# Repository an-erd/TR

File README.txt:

PURPOSE
=======
The function of TR is to have a tiny gym timer, which can give you intervals for active and rest
phases during gym or any other sport. Is has 4 buttons (1 reset button, and three functional
buttons T1..3 ), 9 leds (5 red as a progress bar, 3 orange for current phase active or rest, 
resp. (or during config), and a green heartbeat led.)
It is build on an ATMEL ATMEGA328P, but should work on any other similar MCU, too.
The power is assumed to be 3V. The code is optimized for power saving, but since the leds draw a
pretty high load, it is - by system - still consuming around 10 mA on average during training.

The program flow exist of the following steps:
- initialization (I/O pins, timer, ...)
- configuration routine
- training routine

During the phases, to control is done with the buttons, and the leds change the mode accordingly.
The specific status and control is shown in the list below.

The program itself makes heavy use of two timer, and pin change interrupts. The logic itself, in 
particular waiting for a counter to run down and to give effects and progress with the leds is
more or less completly delivered by the relevant interrupts. 

During WAITING MODE
====================
	LED PB1/green		-> slow flashing means "waiting for command"
	T1					-> choose subprog (timer, metronome, light effects)
	T2					-> go into config mode
	T3					-> GO! (fire chosen subprog)

	LED PD0..7/red/ora	-> off
	LED PB1/green		-> short heartbeat

During CHOOSE_SUBPROG
=====================
	T1					-> increase subprog counter w/wrap-around
	T2					-> n/a
	T3					-> exit choose subprog function

	LED PD0..4/red		-> show configurated value
	LED PD5..7/orange	-> n/a = OFF
	LED PB1/green		-> fast flashing

During CONFIG
=============
	T1					-> increase config parameter value, wrap-arolund 5 -> 1 or 0 resp.
	T2					-> switch to next config parameter, wrap-around is done
	T3					-> GO! fire chosen subprog)

	LED PD0..4/red		-> show configurated value
	LED PD5..7/orange	-> show configuration step (000/INT, 100/ACT, 110/REST, 111/cycles)
	LED PB1/green		-> fast flashing

During TRAINING
===============
	T1					-> (nothing yet)
	T2					-> Stop training and go in "waiting mode", see main loop
	T3					-> Pause training

	LED PD0..4/red		-> show progress in current phase, current step flashes, 1-5 leds
	LED PD5..7/orange	-> show LR or RL cascade to show phase ACTIVE or REST, resp.
	LED PB1/green		-> heartbeat

During PAUSE
============
	LED PD0..4/red		-> freeze current status 
	LED PD5..7/orange	-> freeze current status
	LED PB1/green		-> slow flashing

	T2					-> Stop training/pause and go in "waiting mode", see main loop
	T3					-> end pause, 

TODO and optimization
=====================
- none yet

EEPROM usage for permanently store configuration parameter
==========================================================
uint8_t	EEMEM subprog_param_ee: goes to program_status.subprog_param
set to 
    SUBPROG_TIMER
    SUBPROG_METRONOME
    SUBPROG_LIGHT_EFFECT

uint8_t	EEMEM config_params_ee[NUM_SUBPROGS][NUM_CONFIG_PARAMS] to store values in(maybe a little waste of space)

Timer calculation/values
========================
- 8 MHz quartz, fuse CKDIV8 disabled, F_CPU=8000000UL
- timer0: 8 MHz,  8bit, 1/64  prescale -> 1 KHz (OCR0A   125 ticks / .001s=1ms)
- timer1: 8 MHz, 16bit, 1/256 prescale -> 1 Hz  (OCR1A 31250 Ticks / 1s, OCR1B 3125 Ticks / .1s)

- 8 MHz quartz, fuse CKDIV8 set, F_CPU=1000000UL
- timer0: @F_CPU/8, tick values stay unchanged
- timer1: @F_CPU/64, 1 Hz: OCR1A = 15625, 10 Hz: OCR1B =  1562

FUSE Settings are:
==================
BODLEVEL = 1V8
RSTDISBL = [ ]
DWEN = [ ]
SPIEN = [X]
WDTON = [ ]
EESAVE = [X]
BOOTSZ = 2048W_3800
BOOTRST = [ ]
CKDIV8 = [X]
CKOUT = [ ]
SUT_CKSEL = EXTXOSC_8MHZ_XX_16KCK_14CK_65MS

EXTENDED = 0xFE (valid)
HIGH = 0xD1 (valid)
LOW = 0x7F (valid)

Compiler symbols defined
========================
F_CPU=1000000UL
_PRODUCTION_TEST_ROUTINE_
_ALL_LED_ON_FOR_5_SEC_
_INCREASE_NUM_LED_ON_

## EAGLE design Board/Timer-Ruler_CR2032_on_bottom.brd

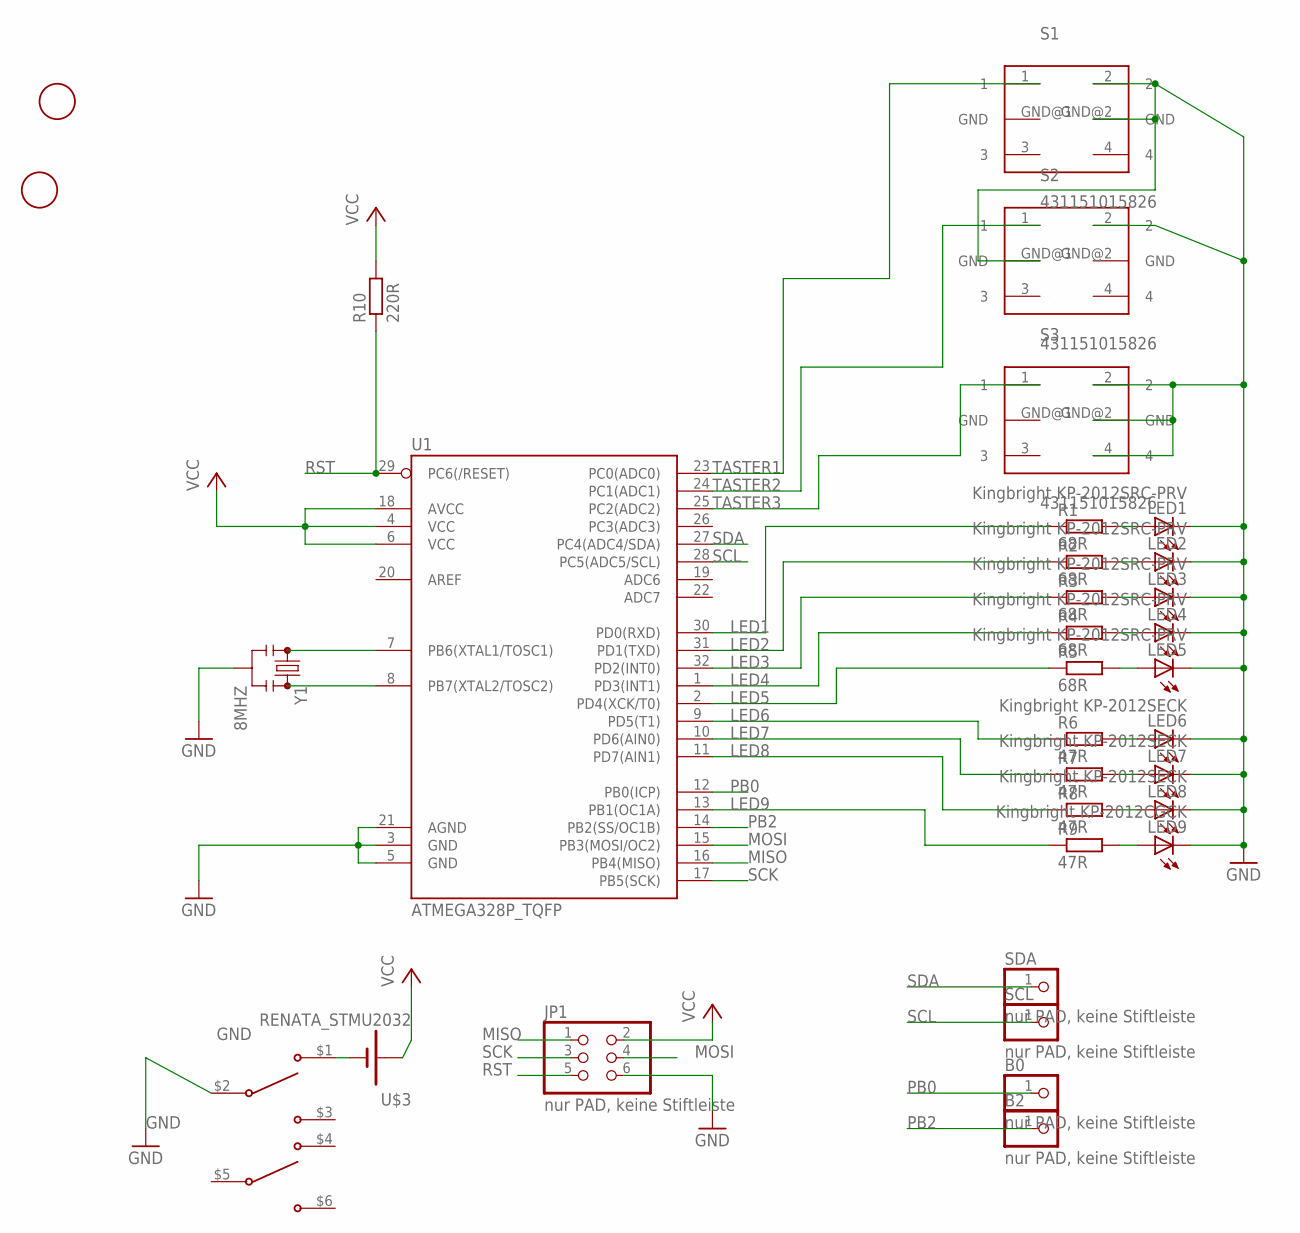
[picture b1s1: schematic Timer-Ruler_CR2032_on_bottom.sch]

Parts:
B0, B2: nur PAD, keine Stiftleiste; 1X01
JP1: nur PAD, keine Stiftleiste; 2X03
LED1, LED2, LED3, LED4, LED5: Kingbright KP-2012SRC-PRV; CHIP-LED0805
LED6, LED7, LED8: Kingbright KP-2012SECK; CHIP-LED0805
LED9: Kingbright KP-2012CGCK; CHIP-LED0805
R1, R2, R3, R4, R5: 68R; R0402
R6, R7, R8, R9: 47R; R0402
R10: 220R; R0402
S1, S2, S3: 431151015826; 431181015816
SCL: nur PAD, keine Stiftleiste; 1X01
SDA: nur PAD, keine Stiftleiste; 1X01
U1: ATMEGA328P_TQFP; TQFP32-08
U$1, U$2: FIDUCIAL; FIDUCIAL_1MM
U$3: RENATA_STMU2032; SMTU2032
U$4: C+K_AYZ0202AGRLC
Y1: 8MHZ; RESONATOR-SMD

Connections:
GND: JP1.6, LED1.C, LED2.C, LED3.C, LED4.C, LED5.C, LED6.C, LED7.C, LED8.C, LED9.C, S1.2, S1.GND@2 (GND), S2.2, S2.GND@1 (GND), S3.2, S3.4, S3.GND@2 (GND), U1.3 (GND), U1.5 (GND), U1.21 (AGND), U$4.$2 (2), Y1.2
LED1: R1.1, U1.30 (PD0(RXD))
LED2: R2.1, U1.31 (PD1(TXD))
LED3: R3.1, U1.32 (PD2(INT0))
LED4: R4.1, U1.1 (PD3(INT1))
LED5: R5.1, U1.2 (PD4(XCK/T0))
LED6: R6.1, U1.9 (PD5(T1))
LED7: R7.1, U1.10 (PD6(AIN0))
LED8: R8.1, U1.11 (PD7(AIN1))
LED9: R9.1, U1.13 (PB1(OC1A))
MISO: JP1.1, U1.16 (PB4(MISO))
MOSI: JP1.4, U1.15 (PB3(MOSI/OC2))
unnamed: LED1.A, R1.2
unnamed: LED2.A, R2.2
unnamed: LED3.A, R3.2
unnamed: LED4.A, R4.2
unnamed: LED5.A, R5.2
unnamed: LED6.A, R6.2
unnamed: LED7.A, R7.2
unnamed: LED8.A, R8.2
unnamed: LED9.A, R9.2
unnamed: U1.7 (PB6(XTAL1/TOSC1)), Y1.1
unnamed: U1.8 (PB7(XTAL2/TOSC2)), Y1.3
unnamed: U$3.-, U$4.$1 (1)
PB0: B0.1, U1.12 (PB0(ICP))
PB2: B2.1, U1.14 (PB2(SS/OC1B))
RST: JP1.5, R10.1, U1.29 (PC6(/RESET))
SCK: JP1.3, U1.17 (PB5(SCK))
SCL: SCL.1, U1.28 (PC5(ADC5/SCL))
SDA: SDA.1, U1.27 (PC4(ADC4/SDA))
TASTER1: S1.1, U1.23 (PC0(ADC0))
TASTER2: S2.1, U1.24 (PC1(ADC1))
TASTER3: S3.1, U1.25 (PC2(ADC2))
VCC: JP1.2, R10.2, U1.4 (VCC), U1.6 (VCC), U1.18 (AVCC), U$3.+

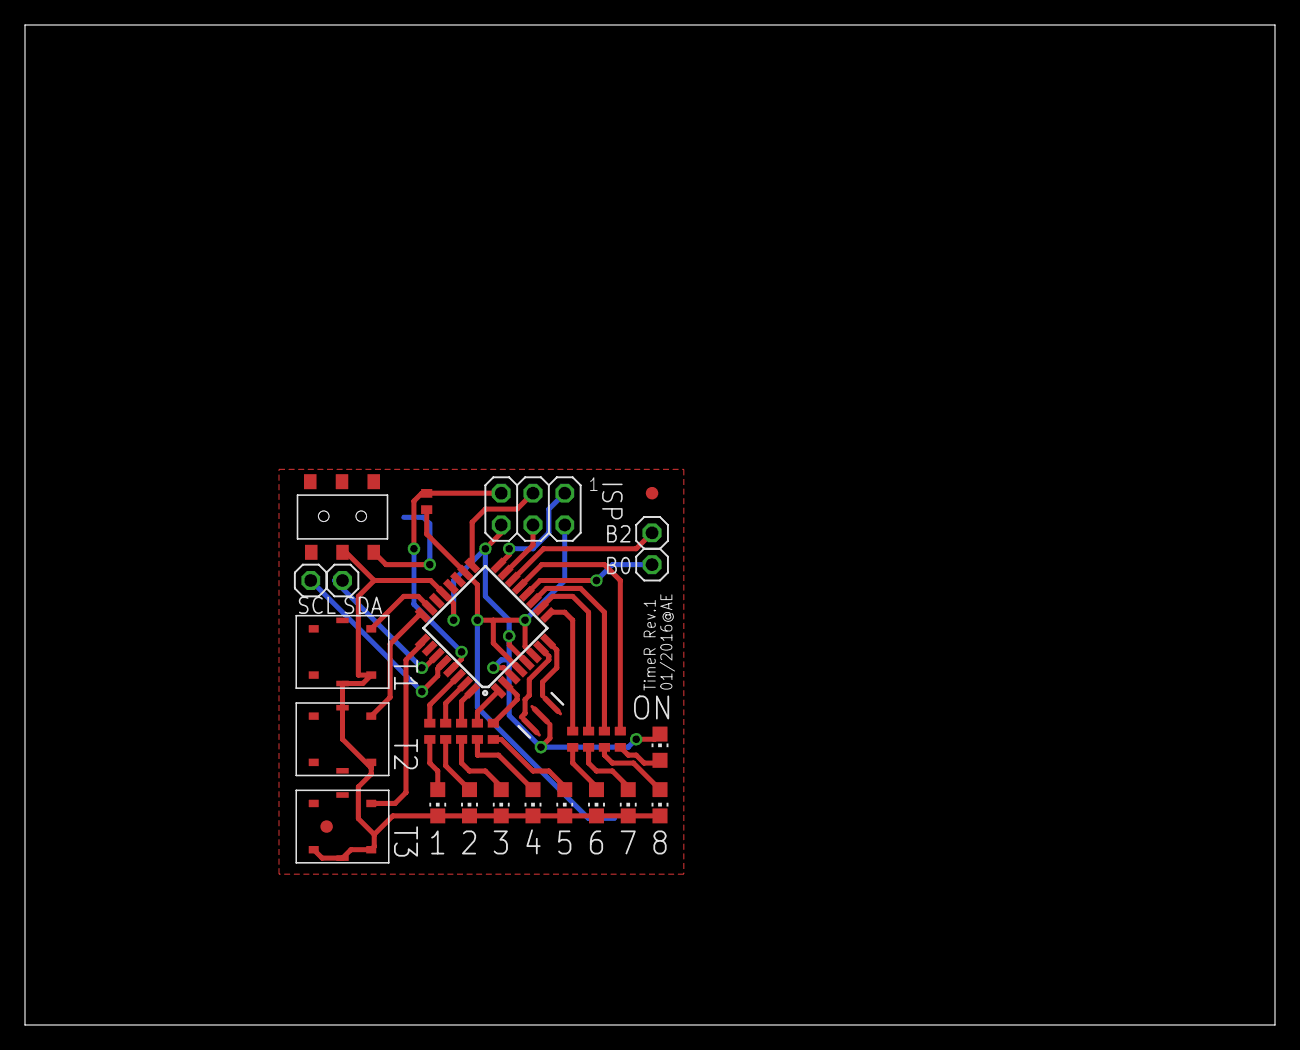
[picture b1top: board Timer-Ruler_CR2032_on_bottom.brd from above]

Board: 2 copper layers, 100.0 x 80.0 mm, 33 parts (1 on the bottom side), 34 nets.

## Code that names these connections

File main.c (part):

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 */ 

/* atmega328p ports used:
	 PC0	Switch T1	PCINT8		0
	 PC1	Switch T2	PCINT9		1
	 PC2	Switch T3	PCINT10		2
	(PC4	I2C SDA		unused)
	(PC5	I2C SCL		unused)
	 PD0	LED1 RED				0
	 PD1	LED2 RED				1
	 PD2	LED3 RED				2
	 PD3	LED4 RED				3
	 PD4	LED5 RED				4
	 PD5	LED6 ORANGE				5
	 PD6	LED7 ORANGE				6
	 PD7	LED8 ORANGE				7
	 PB1 	LED9 GREEN				8
*/

#include <avr/io.h>
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		
	// fired every 1ms gone

	// button debounce mechanism for T1..3 (PC0..2)
	// - the button is assumed to be stable if "pressed" status occurs 50x (=50ms) in a row
	// - temp_state_button_pressed is set in pin change interrupt routine (ISR (PCINT1_vect))
	//
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{
	volatile uint8_t changedbits;

	// Interrupt routine handles pin chance interrupts for PC0..2
	// if a button changes the state, .temp_state_button_pressed is updated
	// results are evaluated (in particular, debouncing) in ISR (TIMER0_COMPA_vect), 
	// and used throughout the program by program_status.Tx.button_pressed, which then need to be cleared again
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void init_io_pins(void)
{
	// power consumption 480 uA in IDLE mode -> 20.8 uA PWR_DOWN
	DDRB  = BIT(DDB1);				// PB1 as output, all other as input
	PORTB = 0xFD;					// all input w/pull-ups
	DDRC  = 0x00;					// all port C as input
	PORTC = 0x7F;					// PC0..2 used for switches, but set all w/pull-ups
	DDRD  = 0xFF;					// all port D as output (all PD0..7 used for LEDs)
	
	bit_set(PCICR,  BIT(PCIE1));							// pin change interrupt enable
	bit_set(PCMSK1, BIT(PCINT8)|BIT(PCINT9)|BIT(PCINT10) );	// Enable pin change detection
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	//		2 -> CONFIG_NR_INTERVAL_REST
	//		3 -> CONFIG_NR_CYCLES
	// do
	//		update orange leds PD5..7 with 0 to all three leds according to i
	//		press T1 X-times -> red leds PD0..4 show the count according to the click counter
	//		press T2 for next step in "for i" loop and wraparound 0->1->2->3->0
	//			or press T3 to leave configuration mode and GO!
	//	done
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	uint8_t temp_multiplied_interval_length;
	
	// current steps blinks .5 Hz (on/off in 2 secs), completed steps on,
	// orange leds PB5..7 show phase (ACTIVE: L->R, REST: R->L)

	// calculation of red leds PB0..4 (L->R)
	// for ACTIVE phase:
	temp_multiplied_interval_length =
		temp_interval_basis_sec * program_status.config_params[program_status.subprog_param][CONFIG_NR_INTERVAL_ACTIVE];
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		do { 
			// in-cycle 2-step loop
			// Complete an ACTIVE or REST phase:
			//	a) update red leds (PD0..4) for in-phase progress regularly
			//	b) update orange leds (PD5..7) for training phase ACTIVE (L->R)/REST (R->L)
			//	c) green led stays in heartbeat mode
			bit_clear(PORTD, LED_PORTD_RED);
			all_led_effect_and_wait_to_complete(in_cycle_steps_done);
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
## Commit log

2015-12-24 Initial checkin
2015-12-24 removed unused parts, moved config_params_min_max to main.c, cleanup
2015-12-24 cosmetic
2015-12-24 #define cleanup, update in main.c
2015-12-24 just code cleanup
2015-12-24 change vars to button
2015-12-24 code cleanup, removed unused parts, loop instead of unrolled loops
2015-12-25 code cleanup, testing, cosmetic
    refactoring of button handling should be completed
2015-12-25 cleanup
2015-12-25 .led_steps_threshold size reduced, usage updated
2015-12-25 moved PINChistory to main.c as global variable
2015-12-25 power optimization added for main prog and perform_config()
    power optimization using sleep() (using IDLE mode) and deep_sleep()
    using PWR_DOWN added for functions main program, configuration.
    perform_training() needs to be done next.
2015-12-25 power optimization for perform_training() added, code cleanup, new function go_to_appropriate_sleep_mode()
2015-12-26 adjusted deep sleep threshold
2015-12-26 updated README.txt
2015-12-26 corrected bug in T1 handling during perform_config()
2015-12-28 moved routine from 1ms-Interrupt to 1s-Interrupt, defect with threshold handly solved
2015-12-28 enabled sleep mode again
2015-12-29 disabled WDT
2015-12-29 Recalculated timer0/1 values, added info to README.txt
    Recalculated timer values for 8 MHz quartz with CKDIV8 set, also added
    information about calculation and FUSE settings/COMPILER symbols to
    README.txt
2015-12-29 BODLEVEL adjusted
2015-12-29 checked power consumption and added results to code/README.txt
2015-12-29 power consumption calculation, evaluated mA for each led an basic consumption
2015-12-30 updated power consumption docs
2015-12-30 added accidently removed code segment again, fully working version now
2016-01-06 updated EEPROM access according to issues #12, #13, #14
    - Use update, not write for EEPROM #12
    - Check that EEPROM is ready before next action #13
    - Deactivate interrupts before write #14
2016-01-06 rewrite of orange led effect code
    solved issue #15 undefined orange led flickering
2016-01-07 first rewrite done
    - added array for ALL LED EFFECT
    - using same counter for effects (orange/red leds)
    - resorted constants
    - still uncomfortable handling for fire effects (pre/post tasks) ->
    needs to be sorted out
    - test, test, test necessary!!!
2016-01-07 adjustments for exit_training_immediately
2016-01-07 added fct led_effect_and_wait_to_complete(), some minor things
2016-01-07 resolved issue w/wrong phase bit set
2016-01-07 added another effect w/all leds ("X" cross), some cleanup
2016-01-08 code cleanup, bit operations, testing, cosmetic
2016-01-10 schematics/board, initial check-in
2016-01-31 initial version of perform_choose_subprog() added
2016-01-31 changed to config_param array (NUM_SUBPROGS*NUM_CONFIG_PARAMS)
    little wast of EEPROM, but since we're using only a small portion,
    everything's fine
2016-01-31 temp checkin, not proven to work correctly
2017-05-20 added fritzing board (produced PCB) and photo
2017-05-20 add photo w/measures

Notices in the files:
parts and their libraries:
SparkFun-DigitalIC: Licensing: Creative Commons ShareAlike 4.0 International - https://creativecommons.org/licenses/by-sa/4.0
Wurth_Elektronik_Electromechanic_Switchs: Copyright: Würth Elektronik
